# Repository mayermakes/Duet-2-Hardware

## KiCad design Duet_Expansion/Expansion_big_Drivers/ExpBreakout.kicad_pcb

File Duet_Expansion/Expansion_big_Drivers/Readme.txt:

Variation on the Expansion Board 1.1 to connect big Stepper drivers (like DM556 etc.)
Easier to Access pins if used with DUEX5
Bigger pads to Solder to / for 5.08mm pitch Screw Terminals
Schematic is mostly unchanged for compability.
Power indicator LED added.

This board was designed for a CNC Blog series by @MAYERMAKES on Element14.com
https://community.element14.com/technologies/motors-and-drives/b/clem-s-cnc-control-project

At the time of writing the Expansion Breakout was unavailable, thanks to the OSHW nature of Duet boards
this was a quick solution to make a Duet2 ethernet work with DM556 Stepper drivers.
Thanks for you commitment to Open source hardware.

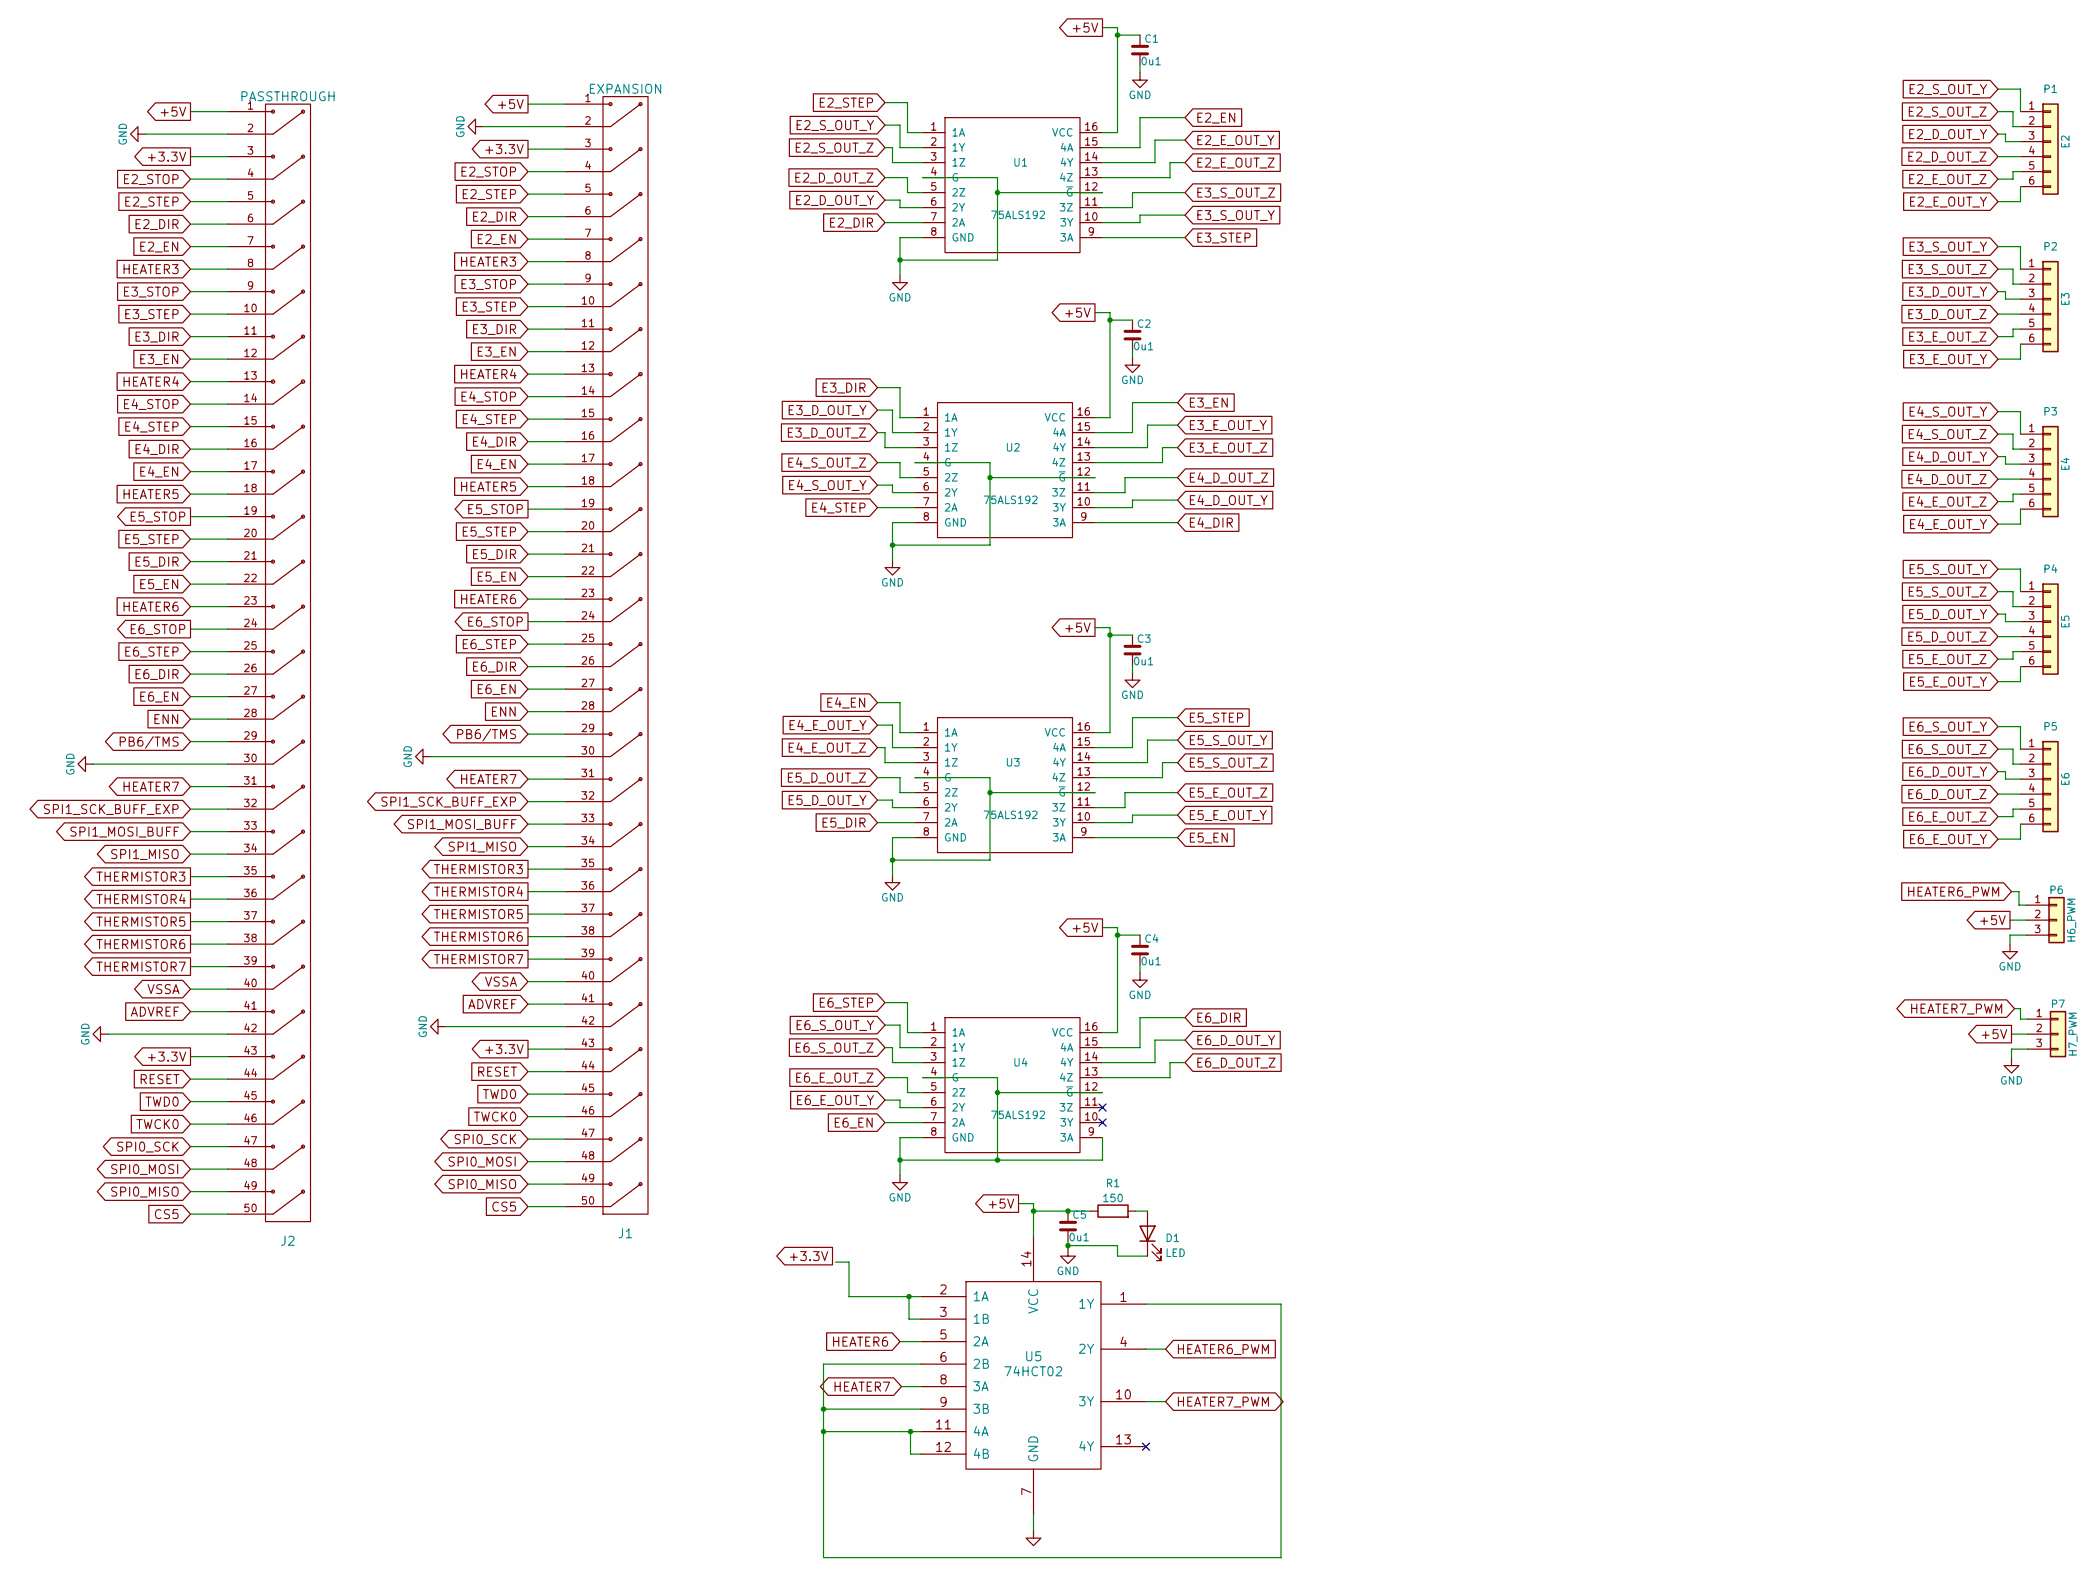
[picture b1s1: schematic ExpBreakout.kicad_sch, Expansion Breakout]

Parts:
C1, C2, C3, C4, C5: 0u1; C_0603_1608Metric
D1: LED; LED_D5.0mm
J1: EXPANSION; PinHeader_2x25_P2.54mm_Vertical
J2: PASSTHROUGH; PinHeader_2x25_P2.54mm_Vertical
P1: E2; TerminalBlock_bornier-6_P5.08mm
P2: E3; TerminalBlock_bornier-6_P5.08mm
P3: E4; TerminalBlock_bornier-6_P5.08mm
P4: E5; TerminalBlock_bornier-6_P5.08mm
P5: E6; TerminalBlock_bornier-6_P5.08mm
P6: H6_PWM; TerminalBlock_bornier-3_P5.08mm
P7: H7_PWM; TerminalBlock_bornier-3_P5.08mm
R1: 150; R_0603_1608Metric
U1, U2, U3, U4: 75ALS192; SOIC-16_3.9x9.9mm_Pitch1.27mm
U5: 74HCT02; TSSOP-14

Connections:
+3.3V: J1.3, J1.43, J2.3, J2.43
+5V: C1.1, C2.1, C3.1, C4.1, C5.1, J1.1, J2.1, P6.2, P7.2, R1.1, U1.16 (VCC), U2.16 (VCC), U3.16 (VCC), U4.16 (VCC), U5.14 (VCC)
ADVREF: J1.41, J2.41
CS5: J1.50, J2.50
E2_DIR: J1.6, J2.6, U1.7 (2A)
E2_D_OUT_Y: P1.3, U1.6 (2Y)
E2_D_OUT_Z: P1.4, U1.5 (2Z)
E2_EN: J1.7, J2.7, U1.15 (4A)
E2_E_OUT_Y: P1.6, U1.14 (4Y)
E2_E_OUT_Z: P1.5, U1.13 (4Z)
E2_STEP: J1.5, J2.5, U1.1 (1A)
E2_STOP: J1.4, J2.4
E2_S_OUT_Y: P1.1, U1.2 (1Y)
E2_S_OUT_Z: P1.2, U1.3 (1Z)
E3_DIR: J1.11, J2.11, U2.1 (1A)
E3_D_OUT_Y: P2.3, U2.2 (1Y)
E3_D_OUT_Z: P2.4, U2.3 (1Z)
E3_EN: J1.12, J2.12, U2.15 (4A)
E3_E_OUT_Y: P2.6, U2.14 (4Y)
E3_E_OUT_Z: P2.5, U2.13 (4Z)
E3_STEP: J1.10, J2.10, U1.9 (3A)
E3_STOP: J1.9, J2.9
E3_S_OUT_Y: P2.1, U1.10 (3Y)
E3_S_OUT_Z: P2.2, U1.11 (3Z)
E4_DIR: J1.16, J2.16, U2.9 (3A)
E4_D_OUT_Y: P3.3, U2.10 (3Y)
E4_D_OUT_Z: P3.4, U2.11 (3Z)
E4_EN: J1.17, J2.17, U3.1 (1A)
E4_E_OUT_Y: P3.6, U3.2 (1Y)
E4_E_OUT_Z: P3.5, U3.3 (1Z)
E4_STEP: J1.15, J2.15, U2.7 (2A)
E4_STOP: J1.14, J2.14
E4_S_OUT_Y: P3.1, U2.6 (2Y)
E4_S_OUT_Z: P3.2, U2.5 (2Z)
E5_DIR: J1.21, J2.21, U3.7 (2A)
E5_D_OUT_Y: P4.3, U3.6 (2Y)
E5_D_OUT_Z: P4.4, U3.5 (2Z)
E5_EN: J1.22, J2.22, U3.9 (3A)
E5_E_OUT_Y: P4.6, U3.10 (3Y)
E5_E_OUT_Z: P4.5, U3.11 (3Z)
E5_STEP: J1.20, J2.20, U3.15 (4A)
E5_STOP: J1.19, J2.19
E5_S_OUT_Y: P4.1, U3.14 (4Y)
E5_S_OUT_Z: P4.2, U3.13 (4Z)
E6_DIR: J1.26, J2.26, U4.15 (4A)
E6_D_OUT_Y: P5.3, U4.14 (4Y)
E6_D_OUT_Z: P5.4, U4.13 (4Z)
E6_EN: J1.27, J2.27, U4.7 (2A)
E6_E_OUT_Y: P5.6, U4.6 (2Y)
E6_E_OUT_Z: P5.5, U4.5 (2Z)
E6_STEP: J1.25, J2.25, U4.1 (1A)
E6_STOP: J1.24, J2.24
E6_S_OUT_Y: P5.1, U4.2 (1Y)
E6_S_OUT_Z: P5.2, U4.3 (1Z)
ENN: J1.28, J2.28
GND: C1.2, C2.2, C3.2, C4.2, C5.2, D1.1 (K), J1.2, J1.30, J1.42, J2.2, J2.30, J2.42, P6.3, P7.3, U1.4 (G), U1.8 (GND), U1.12 (~G), U2.4 (G), U2.8 (GND), U2.12 (~G), U3.4 (G), U3.8 (GND), U3.12 (~G), U4.4 (G), U4.8 (GND), U4.9 (3A), U4.12 (~G), U5.7 (GND)
HEATER3: J1.8, J2.8
HEATER4: J1.13, J2.13
HEATER5: J1.18, J2.18
HEATER6: J1.23, J2.23, U5.5 (2A)
HEATER6_PWM: P6.1, U5.4 (2Y)
HEATER7: J1.31, J2.31, U5.8 (3A)
HEATER7_PWM: P7.1, U5.10 (3Y)
unnamed: D1.2 (A), R1.2
unnamed: U5.1 (1Y), U5.6 (2B), U5.9 (3B), U5.11 (4A), U5.12 (4B)
unnamed: U5.2 (1A), U5.3 (1B)
PB6/TMS: J1.29, J2.29
RESET: J1.44, J2.44
SPI0_MISO: J1.49, J2.49
SPI0_MOSI: J1.48, J2.48
SPI0_SCK: J1.47, J2.47
SPI1_MISO: J1.34, J2.34
SPI1_MOSI_BUFF: J1.33, J2.33
SPI1_SCK_BUFF_EXP: J1.32, J2.32
THERMISTOR3: J1.35, J2.35
THERMISTOR4: J1.36, J2.36
THERMISTOR5: J1.37, J2.37
THERMISTOR6: J1.38, J2.38
THERMISTOR7: J1.39, J2.39
TWCK0: J1.46, J2.46
TWD0: J1.45, J2.45
VSSA: J1.40, J2.40

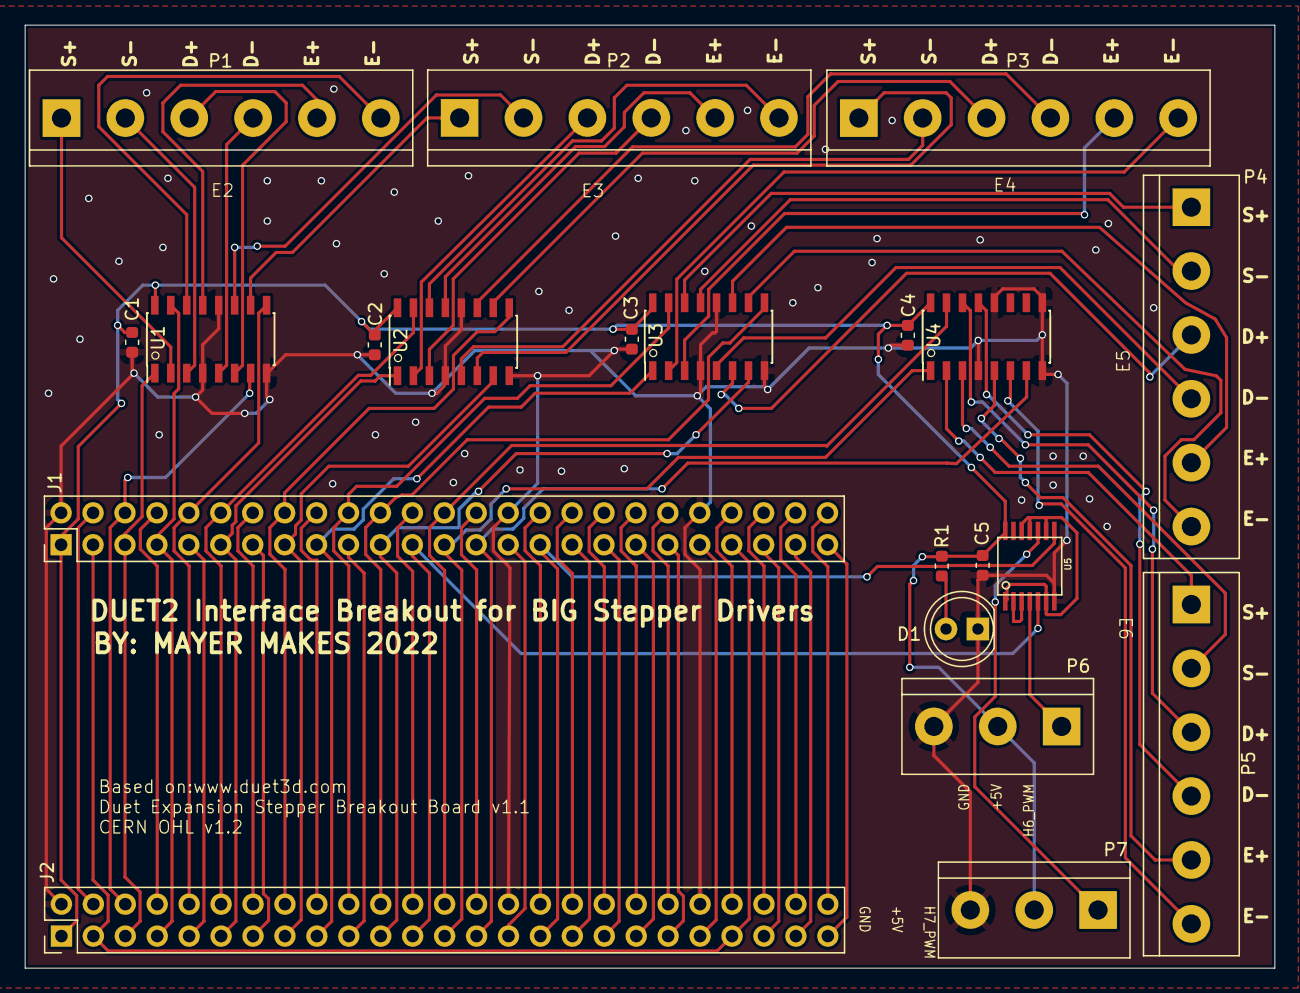
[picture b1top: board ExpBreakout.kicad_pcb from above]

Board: 2 copper layers, 99.4 x 75.0 mm, 21 parts (0 on the bottom side), 82 nets.

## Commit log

2022-11-03 Expansion Breakout Variation for big stepper drivers.

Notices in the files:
Duet_Expansion/Expansion_big_Drivers/ExpBreakout.kicad_pcb:
CERN OHL v1.2
